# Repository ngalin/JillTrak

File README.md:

# JillTrak

A replacement collar transmitter for Deben ferret finders. It works with the
Deben receivers people already have.

Lots of ferreters use Deben finders. The collar goes on the ferret, and the
handheld receiver tells you where it is underground and how deep. Deben has
closed down and you can't buy new collars any more, so if you lose one down a
hole, that's it. We measured a working Deben collar, built our own to match it,
and put everything here so anyone can make one.

*An original Deben collar (left) and one of ours (right).*

If you'd like us to make one for you, email natalia at galinengine dot com.
They cost about US$200.

If you want to support the project, you can [donate here](https://buy.stripe.com/eVq6oJ85U8Ir4Zu3Ao4sE00).

## Where it's at (October 2026)

Our transmitter matches the Deben's signal. We recorded both side by side with
an SDR: same frequency (about 149.1 kHz), same burst length and spacing (11.1 ms
every 184 ms or so), and the signal strength is within about 1 dB.

One difference is that our signal fades slightly over each burst, while the
Deben's stays level. We're working on that in the firmware.

The circuit board works and is ready to order from JLCPCB. The firmware works
on two SR936 cells, and we're testing a new version that should run on a single
CR1632. The 3D-printed case works, but we're still fixing a few fit problems.

We haven't done proper range and depth tests with a Deben receiver yet.

> TODO (Natalia): add the receiver test results when you have them.

## What's in here

- [`background/`](background/): how the Deben works, how we measured it, and how ours compares
- [`Firmware/`](Firmware/): the ATtiny85 code, and how to flash and calibrate a board
- [`hardware/pcb/`](hardware/pcb/): the circuit board, with everything you need to order it
- [`hardware/enclosure/`](hardware/enclosure/): the case STLs, print settings and assembly steps
- [`docs/`](docs/): a one-page overview of the project
- [`tools/`](tools/): our SDR analysis scripts, and the sketch that turns an Arduino into a programmer

## Making your own

Order the board from JLCPCB using the files in [`hardware/pcb/`](hardware/pcb/),
and buy the reed switch and cells separately. Program it with an Arduino Uno
(see [`Firmware/`](Firmware/)), then print the case and put it together (see
[`hardware/enclosure/`](hardware/enclosure/)).

You'll need to be comfortable soldering tiny parts and fine wire, and flashing
firmware. You'll also need an SDR or a Deben receiver to check each board's
frequency.

## Licence

The firmware and tools are under the [MIT licence](LICENSES/MIT.txt), the
hardware under [CERN-OHL-P v2](LICENSES/CERN-OHL-P-2.0.txt), and the
documentation under [CC BY 4.0](LICENSES/CC-BY-4.0.txt). See
[LICENSE.md](LICENSE.md) for details.

We're not connected to Deben in any way. We only use the name to say what this
works with.

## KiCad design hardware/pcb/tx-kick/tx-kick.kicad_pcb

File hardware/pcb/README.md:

# tx-kick: the JillTrak circuit board

A 20 mm round, two-layer board with an ATtiny85, a MOSFET "kick" drive into a
tuned coil, a reed switch, and two pins that take power from the cells.
Several boards have been built and work; one has been run side by side with a
Deben on the same cells.

| Top | Bottom |
|---|---|
|  |  |

Schematic: [`tx-kick/tx-kick-schematic.pdf`](tx-kick/tx-kick-schematic.pdf).

## Getting boards made

Everything JLCPCB needs is in [`tx-kick/`](tx-kick/):

| File | Use |
|---|---|
| `tx-kick-gerbers.zip` | the bare board: copper, mask, paste, silkscreen, outline and drill (upload this first) |
| `tx-kick_bom_jlc.xlsx` (`.csv`) | bill of materials with JLCPCB/LCSC part numbers |
| `tx-kick_cpl_jlc.xlsx` (`.csv`) | placement file: part positions and rotations |
| `digikey_order.csv` | the parts JLCPCB does not fit (reed switch, tank trim capacitors) |

1. Upload `tx-kick-gerbers.zip` at jlcpcb.com. Two layers, **1.6 mm** thick (the case is designed around it), any colour.
2. Turn on **PCB Assembly**, top side. Upload the BOM and placement files.
3. **Check the rotations** in JLCPCB's placement preview before confirming. KiCad and
   JLCPCB's part libraries don't always agree on a part's zero rotation, most often for
   SOT-23 and SOIC parts.
4. **C1 must be C0G/NP0** (it sets the tuning). If the matcher offers an X7R part, reject it.

> TODO (Natalia): the exact JLCPCB options you used (panel or single boards,
> board thickness, quantity), and what the order cost.

## Parts fitted by hand

| Part | What | Notes |
|---|---|---|
| SW1 | Standex-Meder MK24-B-2 reed switch | Fit it **after** programming: it shares the SCK pin (PB2). |
| BT1 | + battery pin, 1.0 mm hole | straight pin or 0.8 mm wire, up through the insert floor |
| BT2 | − battery pin, 1.0 mm hole, centre | |
| L1, L2 | coil ends, 0.7 mm holes | see the coil below |
| C1T | tank trim, 0603 C0G | only if the coil needs tuning down: 1 nF lowers the carrier about 0.5 %, 4.7 nF about 2.3 % |

## The coil

About **19 turns of 0.31 mm enamelled copper wire** in three layers (7, 7, 5),
wound on the printed insert's former, about 23 mm across. With C1 (100 nF) it
tunes to about 149 kHz. Use **solderable polyurethane enamel** (IEC 60317-20 or
-51, sold as "solderable" or "self-fluxing" magnet wire); the iron at 380 to
400 °C strips it as you solder. Ordinary polyester or polyimide enamel has to be
scraped, which is very hard to do on a coil this small.

The coil leads pass through the L1 and L2 holes, through the insert floor, and
are soldered from the cell side. See [the enclosure README](../enclosure/).

## Programming

Four pads: J1.1 to J1.4 are RST (left of the chip), then SCK, MISO and MOSI
(right of the chip, top to bottom). Power comes through the two battery pins.
Wiring and the bring-up order are in the [firmware README](../../Firmware/README.md).
Tack the wires on with strain relief (tape them to the board) and remove them as
soon as programming is done. Loose wires tear the small pads off.

## How the board is made

The layout is generated by Python scripts, not drawn by hand, so it can be
checked and rebuilt:

| File | Role |
|---|---|
| `build_kick.py` | the circuit (netlist), part placement, silkscreen, BOM; writes `tx-kick/tx-kick.kicad_pcb` |
| `router.py`, `route_kick.py`, `route_kick_lib.py` | two-layer router; writes the tracks to `routes_kick.py` |
| `verify_kick.py` | reads the saved board and checks every pin's net against the circuit |
| `check_board.py` | runs KiCad's DRC and renders both sides |
| `schematic_kick.py` | draws the schematic PDF |
| `fplib.py`, `collar.pretty/` | custom footprints: reed switch, battery pins, coil pads, programming pads |
| `fab_kick.py` | JLCPCB BOM, placement and gerber zip |
| `route_all.sh` | all of the above in one go |

```
cd hardware/pcb
python3 -m venv --system-site-packages .venv      # KiCad 7's pcbnew comes from the system
.venv/bin/pip install numpy scipy matplotlib openpyxl
./route_all.sh
```

Open `tx-kick/tx-kick.kicad_pro` in KiCad 7 to view the board. Hand edits made in
KiCad are overwritten if you rerun the scripts. There is no KiCad schematic file:
the netlist in `build_kick.py` is the schematic, and `schematic_kick.py` draws it.

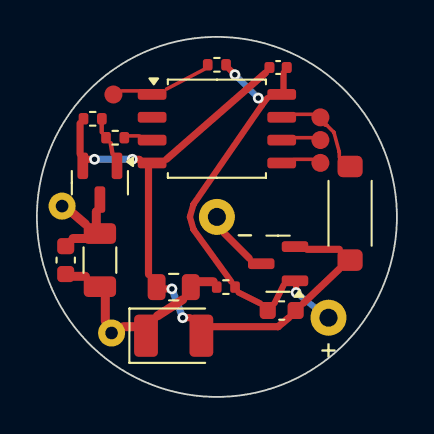
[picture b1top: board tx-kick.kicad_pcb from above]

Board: 2 copper layers, 20.0 x 20.0 mm, 22 parts (0 on the bottom side), 11 nets.

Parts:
BT1: +; Batt_Pos_SidePin_D1.0
BT2: -; Batt_Neg_CentrePin_D1.0
C1: 100n C0G; C_1206_3216Metric
C1T: C0G trim; C_0603_1608Metric
C3: 100n; C_0402_1005Metric
C4: 10u; C_0603_1608Metric
C5: 220u 6.3V; CP_EIA-3528-21_Kemet-B
C5B: 22u; C_0805_2012Metric
J1.1: RST; ISP_Pad_D1.0
J1.2: SCK; ISP_Pad_D1.0
J1.3: MISO; ISP_Pad_D1.0
J1.4: MOSI; ISP_Pad_D1.0
L1: coil A; Coil_Wire_D0.7
L2: coil B; Coil_Wire_D0.7
Q1, Q2: AO3400A; SOT-23
RF: 47; R_0402_1005Metric
RG: 47; R_0402_1005Metric
RPD: 100k; R_0402_1005Metric
RR: 10k; R_0402_1005Metric
SW1: MK24-B-2; Reed_MK24_LeadDesign2
U1: ATtiny85-20SU; SOIC-8_5.23x5.23mm_P1.27mm

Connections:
BATNEG: BT2.1, Q1.3
GATE: Q2.1, RG.2, RPD.1
GND: C3.2, C4.2, C5.2, C5B.2, Q1.2, Q2.2, RPD.2, SW1.2, U1.4
PB0: J1.4.1, U1.5
PB1: J1.3.1, U1.6
PB2: J1.2.1, SW1.1, U1.7
PB4: RG.1, U1.3
RESET: J1.1.1, RR.2, U1.1
TANK_A: C1.1, C1T.1, C5.1, C5B.1, L1.1, RF.2
TANK_B: C1.2, C1T.2, L2.1, Q2.3
VCC: BT1.1, C3.1, C4.1, Q1.1, RF.1, RR.1, U1.8

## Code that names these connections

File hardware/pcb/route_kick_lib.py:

"""Routing of the tx-kick board as a function, for route_kick.py and optimise_kick.py."""
import build_kick as bk
from router import Router

WIDTHS = {"TANK_A": 0.5, "TANK_B": 0.5, "GND": 0.4, "VCC": 0.35, "BATNEG": 0.4,
          "PB4": 0.2, "GATE": 0.25, "RESET": 0.2, "PB2": 0.2, "PB0": 0.2, "PB1": 0.2}
ORDER = ["TANK_A", "TANK_B", "BATNEG", "GND", "VCC", "GATE", "PB4", "RESET", "PB2", "PB1", "PB0"]

def route(order=ORDER, log=print):
    """Place from bk.PARTS and route every net. Returns (tracks, vias, failed)."""
    b, nets = bk.make_board()
    bk.place(b, nets)
    r = Router(b, bk.R_BOARD, WIDTHS)
    failed = []
    for net in order:
        keys = [f"{p}.1" if p.startswith("J1.") else p for p in bk.NETS[net]]   # ISP pads: footprint J1.n, pad 1
        try:
            r.route_net(net, keys); log(f"{net:7} ok")
        except RuntimeError as e:
            log(f"{net:7} FAIL {e}"); failed.append(net)
    return r.tracks, r.vias, failed
